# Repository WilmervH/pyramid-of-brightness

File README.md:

---
name: "Wilmer von Harpe"
slack_id: "U04FR56582F"
github_handle: "@WilmervH"
wokwi: # Link to the Wokwi project
---

# The Pyramid of brightness

Wokwi link: [https://wokwi.com/projects/428436537148664833](https://wokwi.com/projects/428436537148664833)

This was supposed to be a pyramid (or more of a triagle) but I thought I'd be too difficult to arrange the pixels in a neat way. So I made it a square. The name stuck. So Introducing the Pyramid of brightness featuring: USB C connection, sleek design with rounded corners, a whopping 16mb of storage for your precious animations, the power of a pure RP2040, a barometer and a gyroscope.

The baro and gyro were added as fun gimmicks to visualize something real with. Coding without iterating is hard so I'll finish the firmware when I get my board. The purpose of The Pyramid of Brightness is to sit on the corner of my desk and play around with when I'm bored. Also to take to events like LAN parties.

I has this idea of making a snake game where you control the snake by tilting the device. And this is just perfect for that.

## A super rough BOM
| Id          | Designator                  | Footprint                                      | Quantity | Designation                 | cost |
| ----------- | --------------------------- | ---------------------------------------------- | -------- | --------------------------- | ---- |
| 1           | J4                          | SolderJumper-2_P1.3mm_Open_RoundedPad1.0x1.5mm | 1        | Conn_01x02                  | 0    |
| 2           | C18,C16                     | C_0805_2012Metric                              | 2        | 10u                         | 0,1  |
| 3           | C22,C19,C21,C25,C17,C26,C24 | C_0805_2012Metric                              | 7        | 100n                        | 0,2  |
| 4           | R8,R10                      | R_0603_1608Metric                              | 2        | 1K                          | 0,1  |
| 5           | R11,R12                     | R_0603_1608Metric                              | 2        | 27                          | 0,1  |
| 6           | J3                          | USB_C_Receptacle_Amphenol_124019772112A        | 1        | USB_C_Receptacle_USB2.0_14P | 0,7  |
| 7           | U3                          | Texas_RGY_R-PVQFN-N20_EP2.05x3.05mm            | 1        | TXB0108RGY                  | 1    |
| 8           | U5                          | SOT-223-3_TabPin2                              | 1        | NCP1117-3.3_SOT223          | 1    |
| 9           | C23,C20                     | C_0805_2012Metric                              | 2        | 1u                          | 0,1  |
| 10          | X2                          | ABM8-272-T3_ABR                                | 1        | ABM8-272-T3                 | 1    |
| 11          | C14,C15                     | C_0805_2012Metric                              | 2        | 15p                         | 0,1  |
| 12          | R9,R7                       | R_0603_1608Metric                              | 2        | 5K1                         | 0,1  |
| 13          | U6                          | QFN-56-1EP_7x7mm_P0.4mm_EP3.2x3.2mm            | 1        | RP2040                      | 5    |
| 14          | U4                          | SOIC-8_5.3x5.3mm_P1.27mm                       | 1        | W25Q128JVS                  | 1    |
| 15          | R1                          | R_0603_1608Metric                              | 1        | 50K                         | 0,1  |
| 16          | Leds                        | LED_WS2812B-2020_PLCC4_2.0x2.0mm               | 256      | WS2812B-2020                | 10   |
| 17          | C2,C1                       | C_0805_2012Metric                              | 2        | 100nF                       | 0,1  |
| 18          | U2                          | PQFN50P300X250X97-14N                          | 1        | ICM-42688-P                 | 1    |
| 19          | C4                          | C_0805_2012Metric                              | 1        | 0.1uF                       | 0,1  |
| 20          | U1                          | PQFN50P200X200X80-10N                          | 1        | BMP388                      | 1    |
| 21          | C3                          | C_0805_2012Metric                              | 1        | 2.2uF                       | 0,1  |
| 22          | C5                          | C_0805_2012Metric                              | 1        | 10nF                        | 0,1  |
| Rough total |                             |                                                |          | 23                          |

Did I have problems with this. Yes, I did. The Scematic was super fun to make but trying to get Kicad to arrange the leds in a grid or route a differential pair without making huge skews was not fun at all.

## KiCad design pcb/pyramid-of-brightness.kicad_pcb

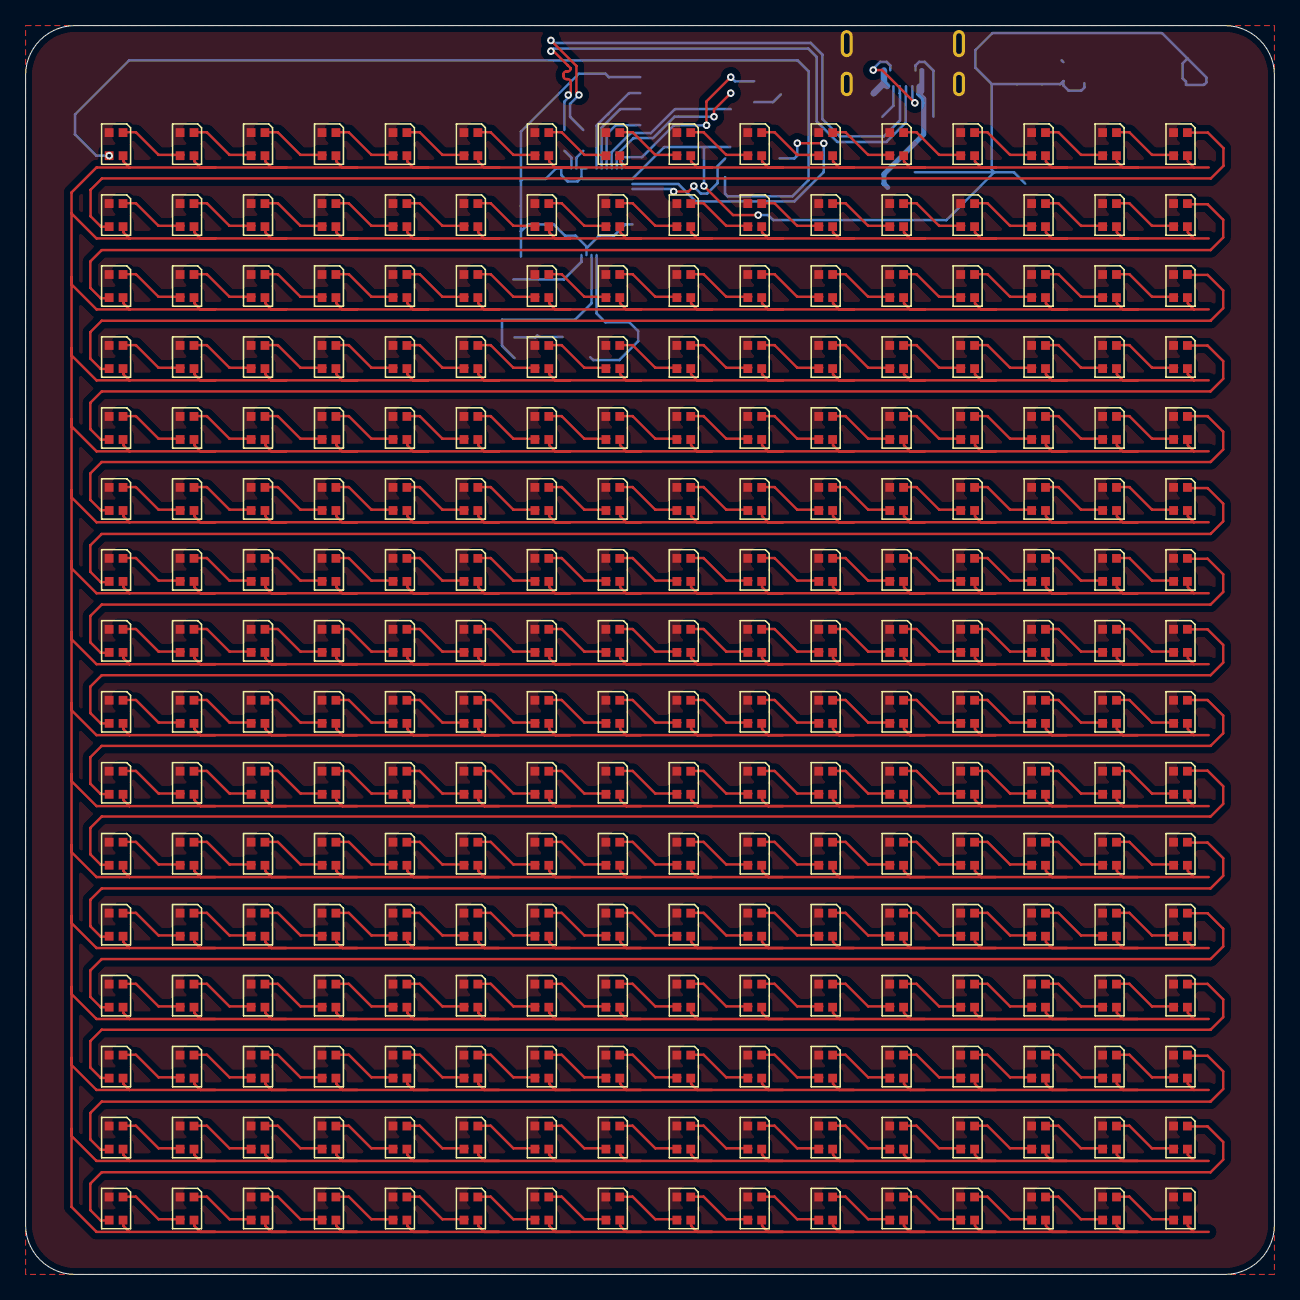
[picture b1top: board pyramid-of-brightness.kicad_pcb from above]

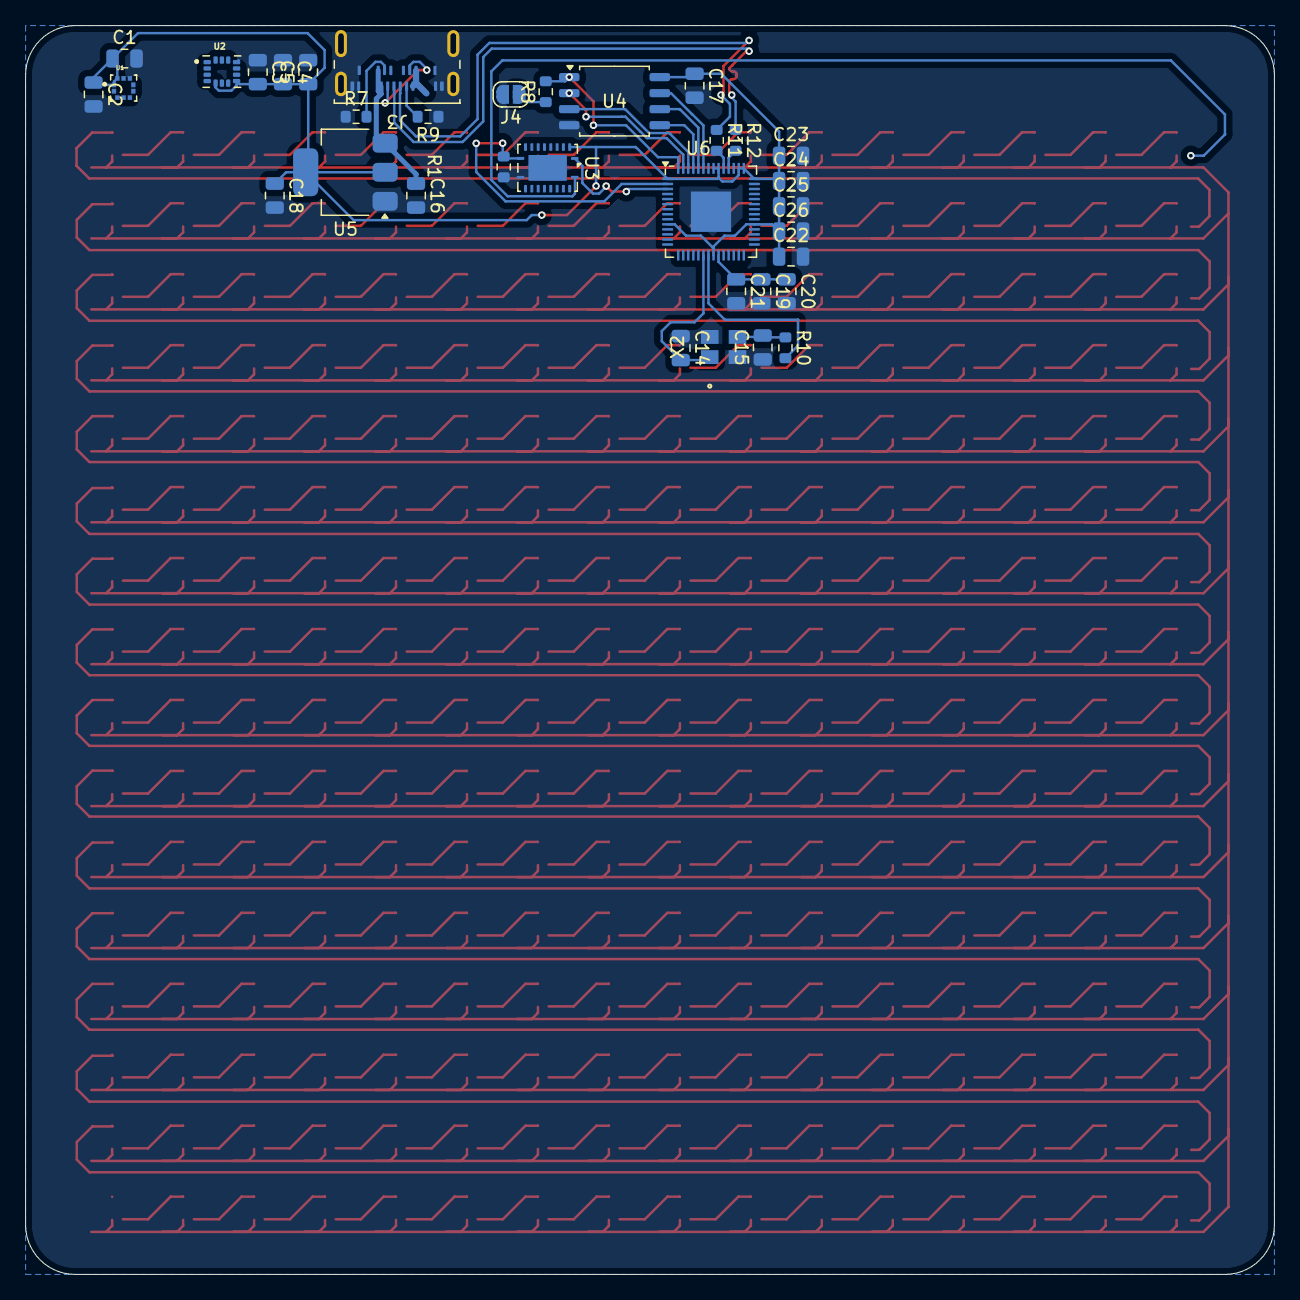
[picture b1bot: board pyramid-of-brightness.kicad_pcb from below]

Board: 2 copper layers, 99.0 x 99.0 mm, 290 parts (34 on the bottom side), 286 nets.

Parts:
C1, C2: 100nF; C_0805_2012Metric
C3: 2.2uF; C_0805_2012Metric
C4: 0.1uF; C_0805_2012Metric
C5: 10nF; C_0805_2012Metric
C14, C15: 15p; C_0805_2012Metric
C16, C18: 10u; C_0805_2012Metric
C17, C19, C21, C22, C24, C25, C26: 100n; C_0805_2012Metric
C20, C23: 1u; C_0805_2012Metric
J3: USB_C_Receptacle_USB2.0_14P; USB_C_Receptacle_Amphenol_124019772112A
J4: Conn_01x02; SolderJumper-2_P1.3mm_Open_RoundedPad1.0x1.5mm
L1001, L1002, L1003, L1004, L1005, L1006, L1007, L1008, L1009, L1010, L1011, L1012, L1013, L1014, L1015, L1016, L1017, L1018, L1019, L1020, L1021, L1022, L1023, L1024, L1025, L1026, L1027, L1028, L1029, L1030, L1031, L1032, L1033, L1034, L1035, L1036, L1037, L1038, L1039, L1040, L1041, L1042, L1043, L1044, L1045, L1046, L1047, L1048, L1049, L1050, L1051, L1052, L1053, L1054, L1055, L1056, L1057, L1058, L1059, L1060, L1061, L1062, L1063, L1064, L1065, L1066, L1067, L1068, L1069, L1070, L1071, L1072, L1073, L1074, L1075, L1076, L1077, L1078, L1079, L1080, L1081, L1082, L1083, L1084, L1085, L1086, L1087, L1088, L1089, L1090, L1091, L1092, L1093, L1094, L1095, L1096, L1097, L1098, L1099, L1100, L1101, L1102, L1103, L1104, L1105, L1106, L1107, L1108, L1109, L1110, L1111, L1112, L1113, L1114, L1115, L1116, L1117, L1118, L1119, L1120, L1121, L1122, L1123, L1124, L1125, L1126, L1127, L1128, L1129, L1130, L1131, L1132, L1133, L1134, L1135, L1136, L1137, L1138, L1139, L1140, L1141, L1142, L1143, L1144, L1145, L1146, L1147, L1148, L1149, L1150, L1151, L1152, L1153, L1154, L1155, L1156, L1157, L1158, L1159, L1160, L1161, L1162, L1163, L1164, L1165, L1166, L1167, L1168, L1169, L1170, L1171, L1172, L1173, L1174, L1175, L1176, L1177, L1178, L1179, L1180, L1181, L1182, L1183, L1184, L1185, L1186, L1187, L1188, L1189, L1190, L1191, L1192, L1193, L1194, L1195, L1196, L1197, L1198, L1199, L1200, L1201, L1202, L1203, L1204, L1205, L1206, L1207, L1208, L1209, L1210, L1211, L1212, L1213, L1214, L1215, L1216, L1217, L1218, L1219, L1220, L1221, L1222, L1223, L1224, L1225, L1226, L1227, L1228, L1229, L1230, L1231, L1232, L1233, L1234, L1235, L1236, L1237, L1238, L1239, L1240, L1241, L1242, L1243, L1244, L1245, L1246, L1247, L1248, L1249, L1250, L1251, L1252, L1253, L1254, L1255, L1256: WS2812B-2020; LED_WS2812B-2020_PLCC4_2.0x2.0mm
R1: 50K; R_0603_1608Metric
R7, R9: 5K1; R_0603_1608Metric
R8, R10: 1K; R_0603_1608Metric
R11, R12: 27; R_0603_1608Metric
U1: BMP388; PQFN50P200X200X80-10N
U2: ICM-42688-P; PQFN50P300X250X97-14N
U3: TXB0108RGY; Texas_RGY_R-PVQFN-N20_EP2.05x3.05mm
U4: W25Q128JVS; SOIC-8_5.3x5.3mm_P1.27mm
U5: NCP1117-3.3_SOT223; SOT-223-3_TabPin2
U6: RP2040; QFN-56-1EP_7x7mm_P0.4mm_EP3.2x3.2mm
X2: ABM8-272-T3; ABM8-272-T3_ABR

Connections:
+1V1: C19.1, C20.1, C21.1, U6.23 (DVDD), U6.45 (VREG_VOUT), U6.50 (DVDD)
+3V3: C1.1, C2.1, C3.2, C4.2, C5.1, C17.1, C18.1, C22.1, C23.1, C24.1, C25.1, C26.1, U1.1 (VDDIO), U1.10 (VDD), U2.5 (VDDIO), U2.8 (VDD), U3.2 (V_{CCA}), U4.8 (VCC), U5.2 (VO), U6.1 (IOVDD), U6.10 (IOVDD), U6.22 (IOVDD), U6.33 (IOVDD), U6.42 (IOVDD), U6.43 (ADC_AVDD), U6.44 (VREG_IN), U6.48 (USB_VDD), U6.49 (IOVDD)
+5V: C16.1, J3.A4 (VBUS), J3.A9 (VBUS), J3.B4 (VBUS), J3.B9 (VBUS), L1001.4 (VDD), L1002.4 (VDD), L1003.4 (VDD), L1004.4 (VDD), L1005.4 (VDD), L1006.4 (VDD), L1007.4 (VDD), L1008.4 (VDD), L1009.4 (VDD), L1010.4 (VDD), L1011.4 (VDD), L1012.4 (VDD), L1013.4 (VDD), L1014.4 (VDD), L1015.4 (VDD), L1016.4 (VDD), L1017.4 (VDD), L1018.4 (VDD), L1019.4 (VDD), L1020.4 (VDD), L1021.4 (VDD), L1022.4 (VDD), L1023.4 (VDD), L1024.4 (VDD), L1025.4 (VDD), L1026.4 (VDD), L1027.4 (VDD), L1028.4 (VDD), L1029.4 (VDD), L1030.4 (VDD), L1031.4 (VDD), L1032.4 (VDD), L1033.4 (VDD), L1034.4 (VDD), L1035.4 (VDD), L1036.4 (VDD), L1037.4 (VDD), L1038.4 (VDD), L1039.4 (VDD), L1040.4 (VDD), L1041.4 (VDD), L1042.4 (VDD), L1043.4 (VDD), L1044.4 (VDD), L1045.4 (VDD), L1046.4 (VDD), L1047.4 (VDD), L1048.4 (VDD), L1049.4 (VDD), L1050.4 (VDD), L1051.4 (VDD), L1052.4 (VDD), L1053.4 (VDD), L1054.4 (VDD), L1055.4 (VDD), L1056.4 (VDD), L1057.4 (VDD), L1058.4 (VDD), L1059.4 (VDD), L1060.4 (VDD), L1061.4 (VDD), L1062.4 (VDD), L1063.4 (VDD), L1064.4 (VDD), L1065.4 (VDD), L1066.4 (VDD), L1067.4 (VDD), L1068.4 (VDD), L1069.4 (VDD), L1070.4 (VDD), L1071.4 (VDD), L1072.4 (VDD), L1073.4 (VDD), L1074.4 (VDD), L1075.4 (VDD), L1076.4 (VDD), L1077.4 (VDD), L1078.4 (VDD), L1079.4 (VDD), L1080.4 (VDD), L1081.4 (VDD), L1082.4 (VDD), L1083.4 (VDD), L1084.4 (VDD), L1085.4 (VDD), L1086.4 (VDD), L1087.4 (VDD), L1088.4 (VDD), L1089.4 (VDD), L1090.4 (VDD), L1091.4 (VDD), L1092.4 (VDD), L1093.4 (VDD), L1094.4 (VDD), L1095.4 (VDD), L1096.4 (VDD), L1097.4 (VDD), L1098.4 (VDD), L1099.4 (VDD), L1100.4 (VDD), L1101.4 (VDD), L1102.4 (VDD), L1103.4 (VDD), L1104.4 (VDD), L1105.4 (VDD), L1106.4 (VDD), L1107.4 (VDD), L1108.4 (VDD), L1109.4 (VDD), L1110.4 (VDD), L1111.4 (VDD), L1112.4 (VDD), L1113.4 (VDD), L1114.4 (VDD), L1115.4 (VDD), L1116.4 (VDD), L1117.4 (VDD), L1118.4 (VDD), L1119.4 (VDD), L1120.4 (VDD), L1121.4 (VDD), L1122.4 (VDD), L1123.4 (VDD), L1124.4 (VDD), L1125.4 (VDD), L1126.4 (VDD), L1127.4 (VDD), L1128.4 (VDD), L1129.4 (VDD), L1130.4 (VDD), L1131.4 (VDD), L1132.4 (VDD), L1133.4 (VDD), L1134.4 (VDD), L1135.4 (VDD), L1136.4 (VDD), L1137.4 (VDD), L1138.4 (VDD), L1139.4 (VDD), L1140.4 (VDD), L1141.4 (VDD), L1142.4 (VDD), L1143.4 (VDD), L1144.4 (VDD), L1145.4 (VDD), L1146.4 (VDD), L1147.4 (VDD), L1148.4 (VDD), L1149.4 (VDD), L1150.4 (VDD), L1151.4 (VDD), L1152.4 (VDD), L1153.4 (VDD), L1154.4 (VDD), L1155.4 (VDD), L1156.4 (VDD), L1157.4 (VDD), L1158.4 (VDD), L1159.4 (VDD), L1160.4 (VDD), L1161.4 (VDD), L1162.4 (VDD), L1163.4 (VDD), L1164.4 (VDD), L1165.4 (VDD), L1166.4 (VDD), L1167.4 (VDD), L1168.4 (VDD), L1169.4 (VDD), L1170.4 (VDD), L1171.4 (VDD), L1172.4 (VDD), L1173.4 (VDD), L1174.4 (VDD), L1175.4 (VDD), L1176.4 (VDD), L1177.4 (VDD), L1178.4 (VDD), L1179.4 (VDD), L1180.4 (VDD), L1181.4 (VDD), L1182.4 (VDD), L1183.4 (VDD), L1184.4 (VDD), L1185.4 (VDD), L1186.4 (VDD), L1187.4 (VDD), L1188.4 (VDD), L1189.4 (VDD), L1190.4 (VDD), L1191.4 (VDD), L1192.4 (VDD), L1193.4 (VDD), L1194.4 (VDD), L1195.4 (VDD), L1196.4 (VDD), L1197.4 (VDD), L1198.4 (VDD), L1199.4 (VDD), L1200.4 (VDD), L1201.4 (VDD), L1202.4 (VDD), L1203.4 (VDD), L1204.4 (VDD), L1205.4 (VDD), L1206.4 (VDD), L1207.4 (VDD), L1208.4 (VDD), L1209.4 (VDD), L1210.4 (VDD), L1211.4 (VDD), L1212.4 (VDD), L1213.4 (VDD), L1214.4 (VDD), L1215.4 (VDD), L1216.4 (VDD), L1217.4 (VDD), L1218.4 (VDD), L1219.4 (VDD), L1220.4 (VDD), L1221.4 (VDD), L1222.4 (VDD), L1223.4 (VDD), L1224.4 (VDD), L1225.4 (VDD), L1226.4 (VDD), L1227.4 (VDD), L1228.4 (VDD), L1229.4 (VDD), L1230.4 (VDD), L1231.4 (VDD), L1232.4 (VDD), L1233.4 (VDD), L1234.4 (VDD), L1235.4 (VDD), L1236.4 (VDD), L1237.4 (VDD), L1238.4 (VDD), L1239.4 (VDD), L1240.4 (VDD), L1241.4 (VDD), L1242.4 (VDD), L1243.4 (VDD), L1244.4 (VDD), L1245.4 (VDD), L1246.4 (VDD), L1247.4 (VDD), L1248.4 (VDD), L1249.4 (VDD), L1250.4 (VDD), L1251.4 (VDD), L1252.4 (VDD), L1253.4 (VDD), L1254.4 (VDD), L1255.4 (VDD), L1256.4 (VDD), U3.19 (V_{CCB}), U5.3 (VI)
/LED_DATA: L1001.3 (DIN), U3.20 (B1)
/Neopixel MATRIX/1: L1016.1 (DOUT), L1017.3 (DIN)
/Neopixel MATRIX/2: L1032.1 (DOUT), L1033.3 (DIN)
/Neopixel MATRIX/3: L1048.1 (DOUT), L1049.3 (DIN)
/Neopixel MATRIX/4: L1064.1 (DOUT), L1065.3 (DIN)
/Neopixel MATRIX/5: L1080.1 (DOUT), L1081.3 (DIN)
/Neopixel MATRIX/6: L1096.1 (DOUT), L1097.3 (DIN)
/Neopixel MATRIX/7: L1112.1 (DOUT), L1113.3 (DIN)
/Neopixel MATRIX/8: L1128.1 (DOUT), L1129.3 (DIN)
/Neopixel MATRIX/9: L1144.1 (DOUT), L1145.3 (DIN)
/Neopixel MATRIX/10: L1160.1 (DOUT), L1161.3 (DIN)
/Neopixel MATRIX/11: L1176.1 (DOUT), L1177.3 (DIN)
/Neopixel MATRIX/12: L1192.1 (DOUT), L1193.3 (DIN)
/Neopixel MATRIX/13: L1208.1 (DOUT), L1209.3 (DIN)
/Neopixel MATRIX/14: L1224.1 (DOUT), L1225.3 (DIN)
/Neopixel MATRIX/15: L1240.1 (DOUT), L1241.3 (DIN)
/OE_SIGNAL: R1.2, U3.10 (OE), U6.2 (GPIO0)
/QSPI_SCLK: U4.6 (CLK), U6.52 (QSPI_SCLK)
/QSPI_SD0: U4.5 (DI/IO_{0}), U6.53 (QSPI_SD0)
/QSPI_SD1: U4.2 (DO/IO_{1}), U6.55 (QSPI_SD1)
/QSPI_SD2: U4.3 (~WP/IO_{2}), U6.54 (QSPI_SD2)
/QSPI_SD3: U4.7 (~HOLD/~RESET/IO_{3}), U6.51 (QSPI_SD3)
/QSPI_SS: R8.2, U4.1 (~CS), U6.56 (QSPI_SS)
/USB D+: J3.A6 (D+), J3.B6 (D+), R11.1
/USB D-: J3.A7 (D-), J3.B7 (D-), R12.1
/USBR_D+: R11.2, U6.47 (USB_DP)
/USBR_D-: R12.2, U6.46 (USB_DM)
/USB_BOOT: J4.1, R8.1
/XIN: C14.2, U6.20 (XIN), X2.1
/XOUT: R10.2, U6.21 (XOUT)
BARO_INT: U1.7 (INT), U6.8 (GPIO6)
GND: C1.2, C2.2, C3.1, C4.1, C5.2, C14.1, C15.1, C16.2, C17.2, C18.2, C19.2, C20.2, C21.2, C22.2, C23.2, C24.2, C25.2, C26.2, J3.A1 (GND), J3.A12 (GND), J3.B1 (GND), J3.B12 (GND), J3.S1 (SHIELD), J4.2, L1001.2 (VSS), L1002.2 (VSS), L1003.2 (VSS), L1004.2 (VSS), L1005.2 (VSS), L1006.2 (VSS), L1007.2 (VSS), L1008.2 (VSS), L1009.2 (VSS), L1010.2 (VSS), L1011.2 (VSS), L1012.2 (VSS), L1013.2 (VSS), L1014.2 (VSS), L1015.2 (VSS), L1016.2 (VSS), L1017.2 (VSS), L1018.2 (VSS), L1019.2 (VSS), L1020.2 (VSS), L1021.2 (VSS), L1022.2 (VSS), L1023.2 (VSS), L1024.2 (VSS), L1025.2 (VSS), L1026.2 (VSS), L1027.2 (VSS), L1028.2 (VSS), L1029.2 (VSS), L1030.2 (VSS), L1031.2 (VSS), L1032.2 (VSS), L1033.2 (VSS), L1034.2 (VSS), L1035.2 (VSS), L1036.2 (VSS), L1037.2 (VSS), L1038.2 (VSS), L1039.2 (VSS), L1040.2 (VSS), L1041.2 (VSS), L1042.2 (VSS), L1043.2 (VSS), L1044.2 (VSS), L1045.2 (VSS), L1046.2 (VSS), L1047.2 (VSS), L1048.2 (VSS), L1049.2 (VSS), L1050.2 (VSS), L1051.2 (VSS), L1052.2 (VSS), L1053.2 (VSS), L1054.2 (VSS), L1055.2 (VSS), L1056.2 (VSS), L1057.2 (VSS), L1058.2 (VSS), L1059.2 (VSS), L1060.2 (VSS), L1061.2 (VSS), L1062.2 (VSS), L1063.2 (VSS), L1064.2 (VSS), L1065.2 (VSS), L1066.2 (VSS), L1067.2 (VSS), L1068.2 (VSS), L1069.2 (VSS), L1070.2 (VSS), L1071.2 (VSS), L1072.2 (VSS), L1073.2 (VSS), L1074.2 (VSS), L1075.2 (VSS), L1076.2 (VSS), L1077.2 (VSS), L1078.2 (VSS), L1079.2 (VSS), L1080.2 (VSS), L1081.2 (VSS), L1082.2 (VSS), L1083.2 (VSS), L1084.2 (VSS), L1085.2 (VSS), L1086.2 (VSS), L1087.2 (VSS), L1088.2 (VSS), L1089.2 (VSS), L1090.2 (VSS), L1091.2 (VSS), L1092.2 (VSS), L1093.2 (VSS), L1094.2 (VSS), L1095.2 (VSS), L1096.2 (VSS), L1097.2 (VSS), L1098.2 (VSS), L1099.2 (VSS), L1100.2 (VSS), L1101.2 (VSS), L1102.2 (VSS), L1103.2 (VSS), L1104.2 (VSS), L1105.2 (VSS), L1106.2 (VSS), L1107.2 (VSS), L1108.2 (VSS), L1109.2 (VSS), L1110.2 (VSS), L1111.2 (VSS), L1112.2 (VSS), L1113.2 (VSS), L1114.2 (VSS), L1115.2 (VSS), L1116.2 (VSS), L1117.2 (VSS), L1118.2 (VSS), L1119.2 (VSS), L1120.2 (VSS), L1121.2 (VSS), L1122.2 (VSS), L1123.2 (VSS), L1124.2 (VSS), L1125.2 (VSS), L1126.2 (VSS), L1127.2 (VSS), L1128.2 (VSS), L1129.2 (VSS), L1130.2 (VSS), L1131.2 (VSS), L1132.2 (VSS), L1133.2 (VSS), L1134.2 (VSS), L1135.2 (VSS), L1136.2 (VSS), L1137.2 (VSS), L1138.2 (VSS), L1139.2 (VSS), L1140.2 (VSS), L1141.2 (VSS), L1142.2 (VSS), L1143.2 (VSS), L1144.2 (VSS), L1145.2 (VSS), L1146.2 (VSS), L1147.2 (VSS), L1148.2 (VSS), L1149.2 (VSS), L1150.2 (VSS), L1151.2 (VSS), L1152.2 (VSS), L1153.2 (VSS), L1154.2 (VSS), L1155.2 (VSS), L1156.2 (VSS), L1157.2 (VSS), L1158.2 (VSS), L1159.2 (VSS), L1160.2 (VSS), L1161.2 (VSS), L1162.2 (VSS), L1163.2 (VSS), L1164.2 (VSS), L1165.2 (VSS), L1166.2 (VSS), L1167.2 (VSS), L1168.2 (VSS), L1169.2 (VSS), L1170.2 (VSS), L1171.2 (VSS), L1172.2 (VSS), L1173.2 (VSS), L1174.2 (VSS), L1175.2 (VSS), L1176.2 (VSS), L1177.2 (VSS), L1178.2 (VSS), L1179.2 (VSS), L1180.2 (VSS), L1181.2 (VSS), L1182.2 (VSS), L1183.2 (VSS), L1184.2 (VSS), L1185.2 (VSS), L1186.2 (VSS), L1187.2 (VSS), L1188.2 (VSS), L1189.2 (VSS), L1190.2 (VSS), L1191.2 (VSS), L1192.2 (VSS), L1193.2 (VSS), L1194.2 (VSS), L1195.2 (VSS), L1196.2 (VSS), L1197.2 (VSS), L1198.2 (VSS), L1199.2 (VSS), L1200.2 (VSS), L1201.2 (VSS), L1202.2 (VSS), L1203.2 (VSS), L1204.2 (VSS), L1205.2 (VSS), L1206.2 (VSS), L1207.2 (VSS), L1208.2 (VSS), L1209.2 (VSS), L1210.2 (VSS), L1211.2 (VSS), L1212.2 (VSS), L1213.2 (VSS), L1214.2 (VSS), L1215.2 (VSS), L1216.2 (VSS), L1217.2 (VSS), L1218.2 (VSS), L1219.2 (VSS), L1220.2 (VSS), L1221.2 (VSS), L1222.2 (VSS), L1223.2 (VSS), L1224.2 (VSS), L1225.2 (VSS), L1226.2 (VSS), L1227.2 (VSS), L1228.2 (VSS), L1229.2 (VSS), L1230.2 (VSS), L1231.2 (VSS), L1232.2 (VSS), L1233.2 (VSS), L1234.2 (VSS), L1235.2 (VSS), L1236.2 (VSS), L1237.2 (VSS), L1238.2 (VSS), L1239.2 (VSS), L1240.2 (VSS), L1241.2 (VSS), L1242.2 (VSS), L1243.2 (VSS), L1244.2 (VSS), L1245.2 (VSS), L1246.2 (VSS), L1247.2 (VSS), L1248.2 (VSS), L1249.2 (VSS), L1250.2 (VSS), L1251.2 (VSS), L1252.2 (VSS), L1253.2 (VSS), L1254.2 (VSS), L1255.2 (VSS), L1256.2 (VSS), R1.1, R7.1, R9.1, U1.3 (VSS), U1.8 (VSS__1), U1.9 (VSS__2), U2.6 (GND), U2.7 (RESV_7), U2.11 (RESV_11), U3.11 (GND), U3.21 (GND), U4.4 (GND), U5.1 (GND), U6.19 (TESTEN), U6.57 (GND), X2.2, X2.4
GYRO_INT: U2.4 (INT1/INT), U6.15 (GPIO12)
GYRO_INT2: U2.9 (INT2/FSYNC/CLKIN), U6.16 (GPIO13)
unnamed: C15.2, R10.1, X2.3
unnamed: J3.A5 (CC1), R9.2
unnamed: J3.B5 (CC2), R7.2
unnamed: L1001.1 (DOUT), L1002.3 (DIN)
unnamed: L1002.1 (DOUT), L1003.3 (DIN)
unnamed: L1003.1 (DOUT), L1004.3 (DIN)
unnamed: L1004.1 (DOUT), L1005.3 (DIN)
unnamed: L1005.1 (DOUT), L1006.3 (DIN)
unnamed: L1006.1 (DOUT), L1007.3 (DIN)
unnamed: L1007.1 (DOUT), L1008.3 (DIN)
unnamed: L1008.1 (DOUT), L1009.3 (DIN)
unnamed: L1009.1 (DOUT), L1010.3 (DIN)
unnamed: L1010.1 (DOUT), L1011.3 (DIN)
unnamed: L1011.1 (DOUT), L1012.3 (DIN)
unnamed: L1012.1 (DOUT), L1013.3 (DIN)
unnamed: L1013.1 (DOUT), L1014.3 (DIN)
unnamed: L1014.1 (DOUT), L1015.3 (DIN)
unnamed: L1015.1 (DOUT), L1016.3 (DIN)
unnamed: L1017.1 (DOUT), L1018.3 (DIN)
unnamed: L1018.1 (DOUT), L1019.3 (DIN)
unnamed: L1019.1 (DOUT), L1020.3 (DIN)
unnamed: L1020.1 (DOUT), L1021.3 (DIN)
unnamed: L1021.1 (DOUT), L1022.3 (DIN)
unnamed: L1022.1 (DOUT), L1023.3 (DIN)
unnamed: L1023.1 (DOUT), L1024.3 (DIN)
unnamed: L1024.1 (DOUT), L1025.3 (DIN)
unnamed: L1025.1 (DOUT), L1026.3 (DIN)
unnamed: L1026.1 (DOUT), L1027.3 (DIN)
unnamed: L1027.1 (DOUT), L1028.3 (DIN)
unnamed: L1028.1 (DOUT), L1029.3 (DIN)
unnamed: L1029.1 (DOUT), L1030.3 (DIN)
unnamed: L1030.1 (DOUT), L1031.3 (DIN)
unnamed: L1031.1 (DOUT), L1032.3 (DIN)
unnamed: L1033.1 (DOUT), L1034.3 (DIN)
unnamed: L1034.1 (DOUT), L1035.3 (DIN)
unnamed: L1035.1 (DOUT), L1036.3 (DIN)
unnamed: L1036.1 (DOUT), L1037.3 (DIN)
unnamed: L1037.1 (DOUT), L1038.3 (DIN)
unnamed: L1038.1 (DOUT), L1039.3 (DIN)
unnamed: L1039.1 (DOUT), L1040.3 (DIN)
unnamed: L1040.1 (DOUT), L1041.3 (DIN)
unnamed: L1041.1 (DOUT), L1042.3 (DIN)
unnamed: L1042.1 (DOUT), L1043.3 (DIN)
unnamed: L1043.1 (DOUT), L1044.3 (DIN)
unnamed: L1044.1 (DOUT), L1045.3 (DIN)
unnamed: L1045.1 (DOUT), L1046.3 (DIN)
unnamed: L1046.1 (DOUT), L1047.3 (DIN)
unnamed: L1047.1 (DOUT), L1048.3 (DIN)
unnamed: L1049.1 (DOUT), L1050.3 (DIN)
unnamed: L1050.1 (DOUT), L1051.3 (DIN)
unnamed: L1051.1 (DOUT), L1052.3 (DIN)
unnamed: L1052.1 (DOUT), L1053.3 (DIN)
unnamed: L1053.1 (DOUT), L1054.3 (DIN)
unnamed: L1054.1 (DOUT), L1055.3 (DIN)
unnamed: L1055.1 (DOUT), L1056.3 (DIN)
unnamed: L1056.1 (DOUT), L1057.3 (DIN)
unnamed: L1057.1 (DOUT), L1058.3 (DIN)
unnamed: L1058.1 (DOUT), L1059.3 (DIN)
unnamed: L1059.1 (DOUT), L1060.3 (DIN)
unnamed: L1060.1 (DOUT), L1061.3 (DIN)
unnamed: L1061.1 (DOUT), L1062.3 (DIN)
unnamed: L1062.1 (DOUT), L1063.3 (DIN)
unnamed: L1063.1 (DOUT), L1064.3 (DIN)
unnamed: L1065.1 (DOUT), L1066.3 (DIN)
unnamed: L1066.1 (DOUT), L1067.3 (DIN)
unnamed: L1067.1 (DOUT), L1068.3 (DIN)
unnamed: L1068.1 (DOUT), L1069.3 (DIN)
unnamed: L1069.1 (DOUT), L1070.3 (DIN)
unnamed: L1070.1 (DOUT), L1071.3 (DIN)
unnamed: L1071.1 (DOUT), L1072.3 (DIN)
unnamed: L1072.1 (DOUT), L1073.3 (DIN)
unnamed: L1073.1 (DOUT), L1074.3 (DIN)
unnamed: L1074.1 (DOUT), L1075.3 (DIN)
unnamed: L1075.1 (DOUT), L1076.3 (DIN)
unnamed: L1076.1 (DOUT), L1077.3 (DIN)
unnamed: L1077.1 (DOUT), L1078.3 (DIN)
unnamed: L1078.1 (DOUT), L1079.3 (DIN)
unnamed: L1079.1 (DOUT), L1080.3 (DIN)
unnamed: L1081.1 (DOUT), L1082.3 (DIN)
unnamed: L1082.1 (DOUT), L1083.3 (DIN)
unnamed: L1083.1 (DOUT), L1084.3 (DIN)
unnamed: L1084.1 (DOUT), L1085.3 (DIN)
unnamed: L1085.1 (DOUT), L1086.3 (DIN)
unnamed: L1086.1 (DOUT), L1087.3 (DIN)
unnamed: L1087.1 (DOUT), L1088.3 (DIN)
unnamed: L1088.1 (DOUT), L1089.3 (DIN)
unnamed: L1089.1 (DOUT), L1090.3 (DIN)
unnamed: L1090.1 (DOUT), L1091.3 (DIN)
unnamed: L1091.1 (DOUT), L1092.3 (DIN)
unnamed: L1092.1 (DOUT), L1093.3 (DIN)
unnamed: L1093.1 (DOUT), L1094.3 (DIN)
unnamed: L1094.1 (DOUT), L1095.3 (DIN)
unnamed: L1095.1 (DOUT), L1096.3 (DIN)
unnamed: L1097.1 (DOUT), L1098.3 (DIN)
unnamed: L1098.1 (DOUT), L1099.3 (DIN)
unnamed: L1099.1 (DOUT), L1100.3 (DIN)
unnamed: L1100.1 (DOUT), L1101.3 (DIN)
unnamed: L1101.1 (DOUT), L1102.3 (DIN)
unnamed: L1102.1 (DOUT), L1103.3 (DIN)
unnamed: L1103.1 (DOUT), L1104.3 (DIN)
unnamed: L1104.1 (DOUT), L1105.3 (DIN)
unnamed: L1105.1 (DOUT), L1106.3 (DIN)
unnamed: L1106.1 (DOUT), L1107.3 (DIN)
unnamed: L1107.1 (DOUT), L1108.3 (DIN)
unnamed: L1108.1 (DOUT), L1109.3 (DIN)
unnamed: L1109.1 (DOUT), L1110.3 (DIN)
unnamed: L1110.1 (DOUT), L1111.3 (DIN)
unnamed: L1111.1 (DOUT), L1112.3 (DIN)
unnamed: L1113.1 (DOUT), L1114.3 (DIN)
unnamed: L1114.1 (DOUT), L1115.3 (DIN)
unnamed: L1115.1 (DOUT), L1116.3 (DIN)
unnamed: L1116.1 (DOUT), L1117.3 (DIN)
unnamed: L1117.1 (DOUT), L1118.3 (DIN)
unnamed: L1118.1 (DOUT), L1119.3 (DIN)
unnamed: L1119.1 (DOUT), L1120.3 (DIN)
unnamed: L1120.1 (DOUT), L1121.3 (DIN)
unnamed: L1121.1 (DOUT), L1122.3 (DIN)
unnamed: L1122.1 (DOUT), L1123.3 (DIN)
unnamed: L1123.1 (DOUT), L1124.3 (DIN)
unnamed: L1124.1 (DOUT), L1125.3 (DIN)
unnamed: L1125.1 (DOUT), L1126.3 (DIN)
unnamed: L1126.1 (DOUT), L1127.3 (DIN)
unnamed: L1127.1 (DOUT), L1128.3 (DIN)
unnamed: L1129.1 (DOUT), L1130.3 (DIN)
unnamed: L1130.1 (DOUT), L1131.3 (DIN)
unnamed: L1131.1 (DOUT), L1132.3 (DIN)
unnamed: L1132.1 (DOUT), L1133.3 (DIN)
unnamed: L1133.1 (DOUT), L1134.3 (DIN)
unnamed: L1134.1 (DOUT), L1135.3 (DIN)
unnamed: L1135.1 (DOUT), L1136.3 (DIN)
unnamed: L1136.1 (DOUT), L1137.3 (DIN)
unnamed: L1137.1 (DOUT), L1138.3 (DIN)
unnamed: L1138.1 (DOUT), L1139.3 (DIN)
unnamed: L1139.1 (DOUT), L1140.3 (DIN)
unnamed: L1140.1 (DOUT), L1141.3 (DIN)
unnamed: L1141.1 (DOUT), L1142.3 (DIN)
unnamed: L1142.1 (DOUT), L1143.3 (DIN)
unnamed: L1143.1 (DOUT), L1144.3 (DIN)
unnamed: L1145.1 (DOUT), L1146.3 (DIN)
unnamed: L1146.1 (DOUT), L1147.3 (DIN)
unnamed: L1147.1 (DOUT), L1148.3 (DIN)
unnamed: L1148.1 (DOUT), L1149.3 (DIN)
unnamed: L1149.1 (DOUT), L1150.3 (DIN)
unnamed: L1150.1 (DOUT), L1151.3 (DIN)
unnamed: L1151.1 (DOUT), L1152.3 (DIN)
unnamed: L1152.1 (DOUT), L1153.3 (DIN)
unnamed: L1153.1 (DOUT), L1154.3 (DIN)
unnamed: L1154.1 (DOUT), L1155.3 (DIN)
unnamed: L1155.1 (DOUT), L1156.3 (DIN)
unnamed: L1156.1 (DOUT), L1157.3 (DIN)
unnamed: L1157.1 (DOUT), L1158.3 (DIN)
unnamed: L1158.1 (DOUT), L1159.3 (DIN)
unnamed: L1159.1 (DOUT), L1160.3 (DIN)
unnamed: L1161.1 (DOUT), L1162.3 (DIN)
unnamed: L1162.1 (DOUT), L1163.3 (DIN)
unnamed: L1163.1 (DOUT), L1164.3 (DIN)
unnamed: L1164.1 (DOUT), L1165.3 (DIN)
unnamed: L1165.1 (DOUT), L1166.3 (DIN)
unnamed: L1166.1 (DOUT), L1167.3 (DIN)
unnamed: L1167.1 (DOUT), L1168.3 (DIN)
unnamed: L1168.1 (DOUT), L1169.3 (DIN)
unnamed: L1169.1 (DOUT), L1170.3 (DIN)
unnamed: L1170.1 (DOUT), L1171.3 (DIN)
unnamed: L1171.1 (DOUT), L1172.3 (DIN)
unnamed: L1172.1 (DOUT), L1173.3 (DIN)
unnamed: L1173.1 (DOUT), L1174.3 (DIN)
unnamed: L1174.1 (DOUT), L1175.3 (DIN)
unnamed: L1175.1 (DOUT), L1176.3 (DIN)
unnamed: L1177.1 (DOUT), L1178.3 (DIN)
unnamed: L1178.1 (DOUT), L1179.3 (DIN)
unnamed: L1179.1 (DOUT), L1180.3 (DIN)
unnamed: L1180.1 (DOUT), L1181.3 (DIN)
unnamed: L1181.1 (DOUT), L1182.3 (DIN)
unnamed: L1182.1 (DOUT), L1183.3 (DIN)
unnamed: L1183.1 (DOUT), L1184.3 (DIN)
unnamed: L1184.1 (DOUT), L1185.3 (DIN)
unnamed: L1185.1 (DOUT), L1186.3 (DIN)
unnamed: L1186.1 (DOUT), L1187.3 (DIN)
unnamed: L1187.1 (DOUT), L1188.3 (DIN)
unnamed: L1188.1 (DOUT), L1189.3 (DIN)
unnamed: L1189.1 (DOUT), L1190.3 (DIN)
unnamed: L1190.1 (DOUT), L1191.3 (DIN)
unnamed: L1191.1 (DOUT), L1192.3 (DIN)
unnamed: L1193.1 (DOUT), L1194.3 (DIN)
unnamed: L1194.1 (DOUT), L1195.3 (DIN)
unnamed: L1195.1 (DOUT), L1196.3 (DIN)
unnamed: L1196.1 (DOUT), L1197.3 (DIN)
unnamed: L1197.1 (DOUT), L1198.3 (DIN)
unnamed: L1198.1 (DOUT), L1199.3 (DIN)
unnamed: L1199.1 (DOUT), L1200.3 (DIN)
unnamed: L1200.1 (DOUT), L1201.3 (DIN)
unnamed: L1201.1 (DOUT), L1202.3 (DIN)
unnamed: L1202.1 (DOUT), L1203.3 (DIN)
unnamed: L1203.1 (DOUT), L1204.3 (DIN)
unnamed: L1204.1 (DOUT), L1205.3 (DIN)
unnamed: L1205.1 (DOUT), L1206.3 (DIN)
unnamed: L1206.1 (DOUT), L1207.3 (DIN)
unnamed: L1207.1 (DOUT), L1208.3 (DIN)
unnamed: L1209.1 (DOUT), L1210.3 (DIN)
unnamed: L1210.1 (DOUT), L1211.3 (DIN)
unnamed: L1211.1 (DOUT), L1212.3 (DIN)
unnamed: L1212.1 (DOUT), L1213.3 (DIN)
unnamed: L1213.1 (DOUT), L1214.3 (DIN)
unnamed: L1214.1 (DOUT), L1215.3 (DIN)
unnamed: L1215.1 (DOUT), L1216.3 (DIN)
unnamed: L1216.1 (DOUT), L1217.3 (DIN)
unnamed: L1217.1 (DOUT), L1218.3 (DIN)
unnamed: L1218.1 (DOUT), L1219.3 (DIN)
unnamed: L1219.1 (DOUT), L1220.3 (DIN)
unnamed: L1220.1 (DOUT), L1221.3 (DIN)
unnamed: L1221.1 (DOUT), L1222.3 (DIN)
unnamed: L1222.1 (DOUT), L1223.3 (DIN)
unnamed: L1223.1 (DOUT), L1224.3 (DIN)
unnamed: L1225.1 (DOUT), L1226.3 (DIN)
unnamed: L1226.1 (DOUT), L1227.3 (DIN)
unnamed: L1227.1 (DOUT), L1228.3 (DIN)
unnamed: L1228.1 (DOUT), L1229.3 (DIN)
unnamed: L1229.1 (DOUT), L1230.3 (DIN)
unnamed: L1230.1 (DOUT), L1231.3 (DIN)
unnamed: L1231.1 (DOUT), L1232.3 (DIN)
unnamed: L1232.1 (DOUT), L1233.3 (DIN)
unnamed: L1233.1 (DOUT), L1234.3 (DIN)
unnamed: L1234.1 (DOUT), L1235.3 (DIN)
unnamed: L1235.1 (DOUT), L1236.3 (DIN)
unnamed: L1236.1 (DOUT), L1237.3 (DIN)
unnamed: L1237.1 (DOUT), L1238.3 (DIN)
unnamed: L1238.1 (DOUT), L1239.3 (DIN)
unnamed: L1239.1 (DOUT), L1240.3 (DIN)
unnamed: L1241.1 (DOUT), L1242.3 (DIN)
unnamed: L1242.1 (DOUT), L1243.3 (DIN)
unnamed: L1243.1 (DOUT), L1244.3 (DIN)
unnamed: L1244.1 (DOUT), L1245.3 (DIN)
unnamed: L1245.1 (DOUT), L1246.3 (DIN)
unnamed: L1246.1 (DOUT), L1247.3 (DIN)
unnamed: L1247.1 (DOUT), L1248.3 (DIN)
unnamed: L1248.1 (DOUT), L1249.3 (DIN)
unnamed: L1249.1 (DOUT), L1250.3 (DIN)
unnamed: L1250.1 (DOUT), L1251.3 (DIN)
unnamed: L1251.1 (DOUT), L1252.3 (DIN)
unnamed: L1252.1 (DOUT), L1253.3 (DIN)
unnamed: L1253.1 (DOUT), L1254.3 (DIN)
unnamed: L1254.1 (DOUT), L1255.3 (DIN)
unnamed: L1255.1 (DOUT), L1256.3 (DIN)
unnamed: U3.1 (A1), U6.3 (GPIO1)
SPI_BARO_CP: U1.6 (CSB), U6.7 (GPIO5)
SPI_GYRO_CP: U2.12 (AP_CS), U6.17 (GPIO14)
SPI_MISO: U1.5 (SDO), U2.1 (AP_SDO/AP_AD0), U6.6 (GPIO4)
SPI_MOSI: U1.4 (SDI), U2.14 (AP_SDA/AP_SDIO/AP_SDI), U6.5 (GPIO3)
SPI_SCK: U1.2 (SCK), U2.13 (AP_SCL/AP_SCLK), U6.4 (GPIO2)

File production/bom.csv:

Designator,Footprint,Quantity,Value,LCSC Part #
"C1, C2",0805,2,100nF,
"C14, C15",0805,2,15p,
"C16, C18",0805,2,10u,
"C17, C19, C21, C22, C24, C25, C26",0805,7,100n,
"C20, C23",0805,2,1u,
C3,0805,1,2.2uF,
C4,0805,1,0.1uF,
C5,0805,1,10nF,
J3,USB_C_Receptacle_Amphenol_124019772112A,1,USB_C_Receptacle_USB2.0_14P,
J4,SolderJumper-2_P1.3mm_Open_RoundedPad1.0x1.5mm,1,Conn_01x02,
"L1001, L1002, L1003, L1004, L1005, L1006, L1007, L1008, L1009, L1010, L1011, L1012, L1013, L1014, L1015, L1016, L1017, L1018, L1019, L1020, L1021, L1022, L1023, L1024, L1025, L1026, L1027, L1028, L1029, L1030, L1031, L1032, L1033, L1034, L1035, L1036, L1037, L1038, L1039, L1040, L1041, L1042, L1043, L1044, L1045, L1046, L1047, L1048, L1049, L1050, L1051, L1052, L1053, L1054, L1055, L1056, L1057, L1058, L1059, L1060, L1061, L1062, L1063, L1064, L1065, L1066, L1067, L1068, L1069, L1070, L1071, L1072, L1073, L1074, L1075, L1076, L1077, L1078, L1079, L1080, L1081, L1082, L1083, L1084, L1085, L1086, L1087, L1088, L1089, L1090, L1091, L1092, L1093, L1094, L1095, L1096, L1097, L1098, L1099, L1100, L1101, L1102, L1103, L1104, L1105, L1106, L1107, L1108, L1109, L1110, L1111, L1112, L1113, L1114, L1115, L1116, L1117, L1118, L1119, L1120, L1121, L1122, L1123, L1124, L1125, L1126, L1127, L1128, L1129, L1130, L1131, L1132, L1133, L1134, L1135, L1136, L1137, L1138, L1139, L1140, L1141, L1142, L1143, L1144, L1145, L1146, L1147, L1148, L1149, L1150, L1151, L1152, L1153, L1154, L1155, L1156, L1157, L1158, L1159, L1160, L1161, L1162, L1163, L1164, L1165, L1166, L1167, L1168, L1169, L1170, L1171, L1172, L1173, L1174, L1175, L1176, L1177, L1178, L1179, L1180, L1181, L1182, L1183, L1184, L1185, L1186, L1187, L1188, L1189, L1190, L1191, L1192, L1193, L1194, L1195, L1196, L1197, L1198, L1199, L1200",LED_WS2812B-2020_PLCC4_2.0x2.0mm,200,WS2812B-2020,
"L1201, L1202, L1203, L1204, L1205, L1206, L1207, L1208, L1209, L1210, L1211, L1212, L1213, L1214, L1215, L1216, L1217, L1218, L1219, L1220, L1221, L1222, L1223, L1224, L1225, L1226, L1227, L1228, L1229, L1230, L1231, L1232, L1233, L1234, L1235, L1236, L1237, L1238, L1239, L1240, L1241, L1242, L1243, L1244, L1245, L1246, L1247, L1248, L1249, L1250, L1251, L1252, L1253, L1254, L1255, L1256",LED_WS2812B-2020_PLCC4_2.0x2.0mm,56,WS2812B-2020,
R1,0603,1,50K,
"R10, R8",0603,2,1K,
"R11, R12",0603,2,27,
"R7, R9",0603,2,5K1,
U1,PQFN50P200X200X80-10N,1,BMP388,
U2,PQFN50P300X250X97-14N,1,ICM-42688-P,
U3,Texas_RGY_R-PVQFN-N20_EP2.05x3.05mm,1,TXB0108RGY,
U4,SOIC-8_5.3x5.3mm_P1.27mm,1,W25Q128JVS,
U5,SOT-223-3_TabPin2,1,NCP1117-3.3_SOT223,
U6,QFN-56-1EP_7x7mm_P0.4mm_EP3.2x3.2mm,1,RP2040,
X2,ABM8-272-T3_ABR,1,ABM8-272-T3,

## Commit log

2025-04-17 made pyramid of brightness
2025-04-21 Finished board
